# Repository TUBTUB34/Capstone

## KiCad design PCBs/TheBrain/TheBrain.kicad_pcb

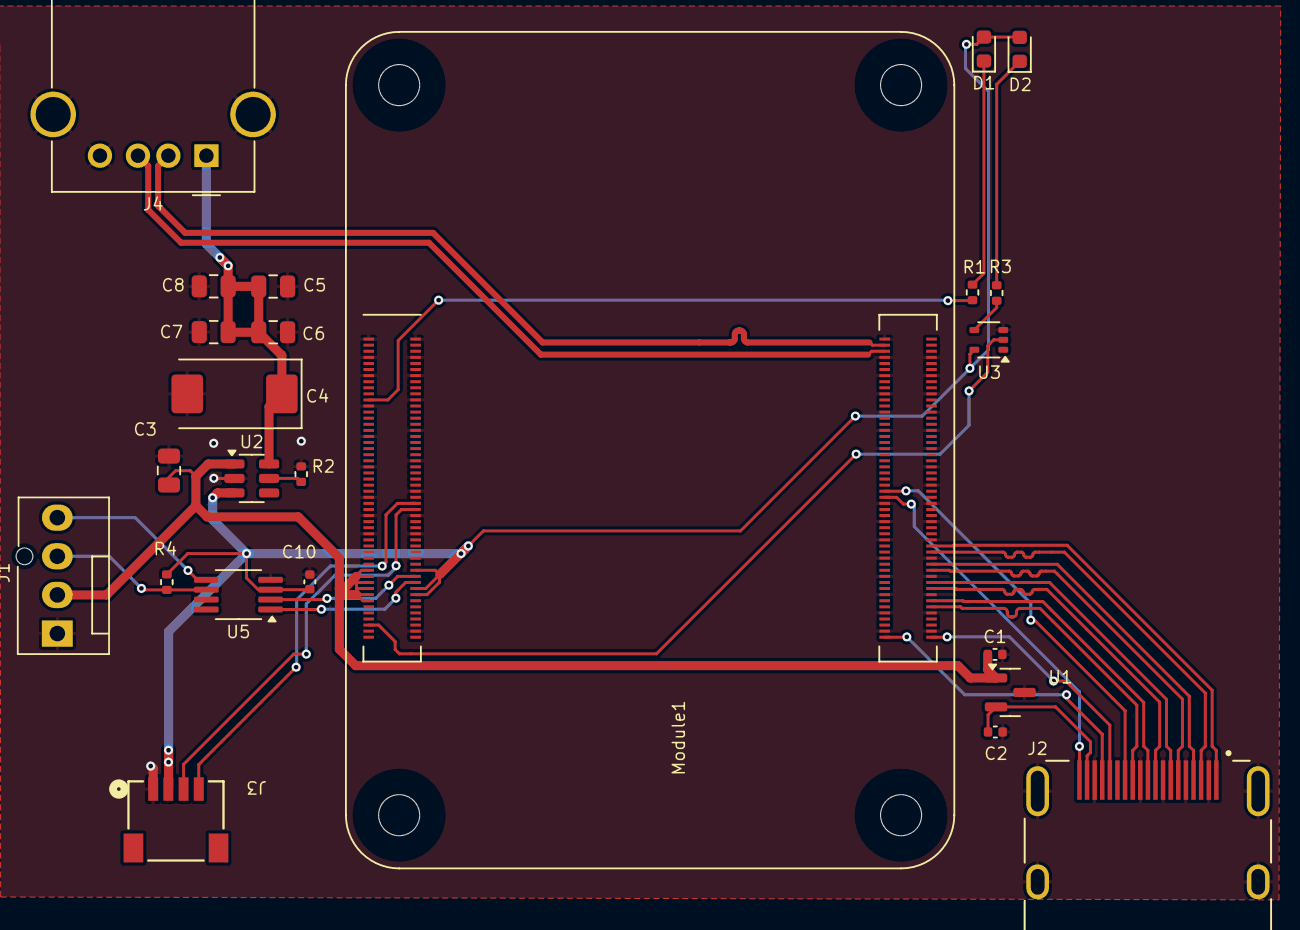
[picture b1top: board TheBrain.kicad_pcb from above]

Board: 2 copper layers, 24 parts (0 on the bottom side), 31 nets.

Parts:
C1, C2, C10: 100n; C_0402_1005Metric
C3, C5, C6, C7, C8: 10u; C_0805_2012Metric
C4: 100uF; CP_EIA-7343-31_Kemet-D
D1: LED Green; LED_0603_1608Metric
D2: LED Red; LED_0603_1608Metric
J1: Molex 470531000; FanPinHeader_1x04_P2.54mm_Vertical
J2: 690-019-298-412; EDAC 690-019-298-412
J3: SM04B-SRSS-TB; CONN_SM04B-SRSS-TB_JST
J4: USB_A; USB_A_Molex_67643_Horizontal
Module1: ComputeModule4; Raspberry-Pi-4-Compute-Module
R1, R3: 1k; R_0402_1005Metric
R2: 15K 1%; R_0402_1005Metric
R4: 36K 1%; R_0402_1005Metric
U1: RT9742SNGV; SOT-23
U2: AP22653W6; SOT-23-6
U3: 74LVC1G07SE-7; SOT-353_SC-70-5
U5: EMC2301-1-ACZL-TR; MSOP-8_3x3mm_P0.65mm

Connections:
/+3.3V: C10.1, D1.2 (A), D2.2 (A), J3.2, Module1.78 (GPIO_VREF(1.8v/3.3v_Input)), Module1.84 (+3.3v_(Output)), Module1.86 (+3.3v_(Output)), R4.2, U2.3 (EN), U3.5 (VCC), U5.3 (VDD)
/+5V: C1.1, C3.1, J1.2, Module1.77 (+5v_(Input)), Module1.79 (+5v_(Input)), Module1.81 (+5v_(Input)), Module1.83 (+5v_(Input)), Module1.85 (+5v_(Input)), Module1.87 (+5v_(Input)), U1.1 (IN), U2.1 (IN)
/CM4 Module/HDMI0_CEC: J2.13 (CEC), Module1.151 (HDMI0_CEC)
/CM4 Module/HDMI0_CK_N: J2.12 (CK-), Module1.190 (HDMI0_CLK_N)
/CM4 Module/HDMI0_CK_P: J2.10 (CK+), Module1.188 (HDMI0_CLK_P)
/CM4 Module/HDMI0_D0_N: J2.9 (D0-), Module1.184 (HDMI0_TX0_N)
/CM4 Module/HDMI0_D0_P: J2.7 (D0+), Module1.182 (HDMI0_TX0_P)
/CM4 Module/HDMI0_D1_N: J2.6 (D1-), Module1.178 (HDMI0_TX1_N)
/CM4 Module/HDMI0_D1_P: J2.4 (D1+), Module1.176 (HDMI0_TX1_P)
/CM4 Module/HDMI0_D2_N: J2.3 (D2-), Module1.172 (HDMI0_TX2_N)
/CM4 Module/HDMI0_D2_P: J2.1 (D2+), Module1.170 (HDMI0_TX2_P)
/CM4 Module/HDMI0_HOTPLUG: J2.19 (HPD/HEAC-), Module1.153 (HDMI0_HOTPLUG)
/CM4 Module/HDMI0_SCL: J2.15 (SCL), Module1.200 (HDMI0_SCL)
/CM4 Module/HDMI0_SDA: J2.16 (SDA), Module1.199 (HDMI0_SDA)
/CM4 Module/SCL0: Module1.80 (SCL0), U5.2 (SCL)
/CM4 Module/SDA0: Module1.82 (SDA0), U5.1 (SDA)
/CM4 Module/SDA1: J3.3, Module1.58 (GPIO2)
/CM4 Module/SDC1: J3.4, Module1.56 (GPIO3)
/CM4 Module/USB2_N: J4.2 (D-), Module1.103 (USB2_N)
/CM4 Module/USB2_P: J4.3 (D+), Module1.105 (USB2_P)
/CM4 Module/nPWR_LED: Module1.95 (nPI_LED_PWR), U3.2
/Connectors/HDMI_5v: C2.1, J2.18 (+5V), U1.2 (OUT)
/Connectors/VBUS: C4.1, C5.1, C6.1, C7.1, C8.1, J4.1 (VBUS), U2.6 (OUT)
GND: C1.2, C2.2, C3.2, C4.2, C5.2, C6.2, C7.2, C8.2, C10.2, J1.1, J2.2 (D2S), J2.5 (D1S), J2.8 (D0S), J2.11 (CKS), J2.17 (GND), J2.SH1 (SH), J2.SH2 (SH), J2.SH3 (SH), J2.SH4 (SH), J3.1, J4.4 (GND), J4.5 (Shield), Module1.1 (GND), Module1.2 (GND), Module1.7 (GND), Module1.8 (GND), Module1.13 (GND), Module1.14 (GND), Module1.22 (GND), Module1.23 (GND), Module1.32 (GND), Module1.33 (GND), Module1.42 (GND), Module1.43 (GND), Module1.52 (GND), Module1.53 (GND), Module1.59 (GND), Module1.60 (GND), Module1.65 (GND), Module1.66 (GND), Module1.71 (GND), Module1.74 (GND), Module1.98 (GND), Module1.101 (USB_OTG_ID), Module1.107 (GND), Module1.108 (GND), Module1.113 (GND), Module1.114 (GND), Module1.119 (GND), Module1.120 (GND), Module1.125 (GND), Module1.126 (GND), Module1.131 (GND), Module1.132 (GND), Module1.137 (GND), Module1.138 (GND), Module1.144 (GND), Module1.150 (GND), Module1.155 (GND), Module1.156 (GND), Module1.161 (GND), Module1.162 (GND), Module1.167 (GND), Module1.168 (GND), Module1.173 (GND), Module1.174 (GND), Module1.179 (GND), Module1.180 (GND), Module1.185 (GND), Module1.186 (GND), Module1.191 (GND), Module1.192 (GND), Module1.197 (GND), Module1.198 (GND), R2.2, U1.3 (GND), U2.2 (GND), U3.3 (GND), U5.4 (GND)
unnamed: D1.1 (K), R1.1
unnamed: D2.1 (K), R3.1
unnamed: J1.3, R4.1, U5.6 (TACH)
unnamed: J1.4, U5.5 (PWM)
unnamed: Module1.21 (PI_nLED_Activity), R1.2
unnamed: R3.2, U3.4
unnamed: R2.1, U2.5 (ILIM)

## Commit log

2024-08-17 QT-PY arduino slave code, GUI Testing
2024-08-17 Updated Test code
2024-08-17 Added some stuff
2024-08-27 Started Brain PCB
